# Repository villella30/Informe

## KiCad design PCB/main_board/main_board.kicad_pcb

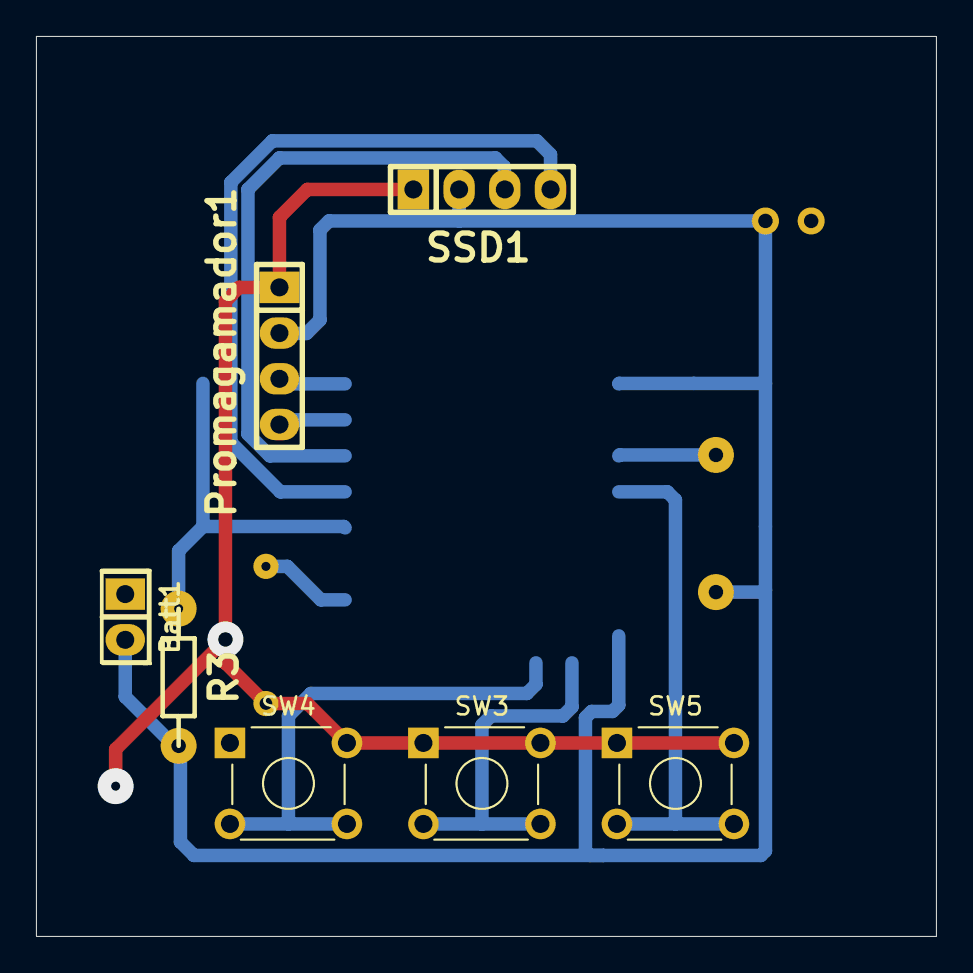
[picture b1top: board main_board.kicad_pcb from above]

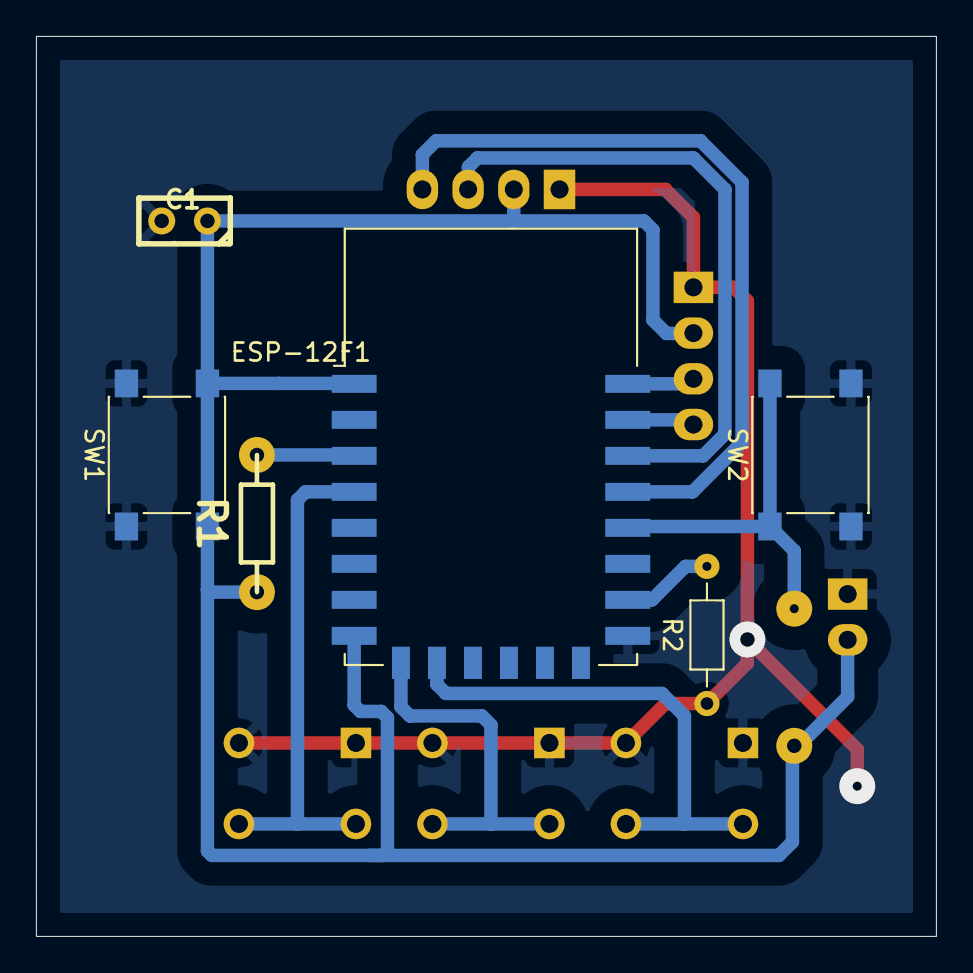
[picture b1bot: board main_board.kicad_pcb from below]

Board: 2 copper layers, 50.0 x 50.0 mm, 13 parts (6 on the bottom side), 12 nets.

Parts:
Batt1: Conn_01x02_Female; Pin_Header_2
C1: 100nF; CAP_0.1
ESP-12F1: ESP-12F; ESP-12E
Promagamador1: Conn_01x04_Female; pin_strip_4
R1, R3: 10k; RES0.3
R2: 10k; R_Axial_DIN0204_L3.6mm_D1.6mm_P7.62mm_Horizontal
SSD1: SSD1306-SSD1306-128x64_OLED; pin_strip_4
SW1: Reset; SW_Push_1P1T_NO_6x6mm_H9.5mm
SW2: Boot; SW_Push_1P1T_NO_6x6mm_H9.5mm
SW3: OK; SW_TH_Tactile_Omron_B3F-10xx
SW4: DOWN; SW_TH_Tactile_Omron_B3F-10xx
SW5: UP; SW_TH_Tactile_Omron_B3F-10xx

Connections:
+3V3: Batt1.2, C1.1, ESP-12F1.1 (~RST), ESP-12F1.8 (VCC), Promagamador1.2, R1.1, R3.2, SSD1.2 (VCC), SW1.2
/P_DOWN: ESP-12F1.10 (MISO), SW4.2
/P_OK: ESP-12F1.9 (CS0), SW3.2
/P_UP: ESP-12F1.4 (GPIO16), SW5.2
/Rx: ESP-12F1.21 (GPIO3/RXD), Promagamador1.4
/SCL: ESP-12F1.20 (GPIO5), SSD1.3 (SCL)
/SDA: ESP-12F1.19 (GPIO4), SSD1.4 (SDA)
/Tx: ESP-12F1.22 (GPIO1/TXD), Promagamador1.3
GND: Batt1.1, C1.2, ESP-12F1.15 (GND), Promagamador1.1, R2.1, SSD1.1 (GND), SW1.1, SW2.2, SW3.1, SW4.1, SW5.1
unnamed: ESP-12F1.3 (EN), R1.2
unnamed: ESP-12F1.16 (GPIO15), R2.2
unnamed: ESP-12F1.18 (GPIO0), R3.1, SW2.1

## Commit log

2022-11-25 Create SmartWatch Schematic
2022-11-25 Create Pcb SmartWatch Prototipo
2022-11-25 Create Pcb mejorado SmartWatch
2022-11-25 Create Programacion SmartWatch
2022-11-25 Rename SmartWatch Schematic to SmartWatch prototipo Schematic
2022-11-25 Create SmartWatch mejorado Schematic
2022-11-29 Create Programacion Reloj
